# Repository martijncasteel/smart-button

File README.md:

# Smart-button
Simple shield for Nodemcu v3 with three cherrymx buttons. The different buttons can control Elgato lights or Hue Lights. This project came forward out the necesity of having a button to control a Elgato keylight without having to use their app.

## Usage
Start by setting up [source/secrets.h](code/smart-button/secrets.h.example) with your wifi credentials and bridge ip-address if you want to add Hue lights. Adjust your smart-button.ino as you wish to use, below some information on setting up the different lights. 

### Elgato Keylight
Controlling a Elgato keylight can be done with the following;
```c++
// connect with light in setup
Light * keyLight = new ElgatoLight("http://elgato-key-light-air-1857.local:9123/elgato/lights");
keyLight->toggle();
```

### Hue Lights and groups
Controlling a Hue light is a little bit more complex, the device needs to create an account on the Hue bridge. When starting the device it will connect to the wifi configured in `secret.h`. When the light is blinking you'll have to press the button on the bridge. When pressed you'll have 30 seconds to press the first button on our shield.
```c++
  // connect to bridge, create and store user in eeprom
  address_t bridge = HueLight::connect(HUE_BRIDGE, LED_BUILTIN, buttons[0]);

  // control a specific light
  Light * diningLight = new HueLight(bridge, 3);

  // controll all lights within a group
  Light * livingRoom = new HueGroup(bridge, 7);
  livingRoom->toggle();
```

## Shield

A simple shield made using Kicad to give it a nice aesthetic, you can also use a simple breadboard with simple buttons. The pins use an interal pull-up resistor. When the pin is connected to ground the button is pressed. You can find the source in [pcb](pcb/) and the assembly in [assembly](assembly/) to send to your preferred manufacturer.

## License
This project is licensed under the MIT license. See [LICENSE](LICENSE.md) for more information.

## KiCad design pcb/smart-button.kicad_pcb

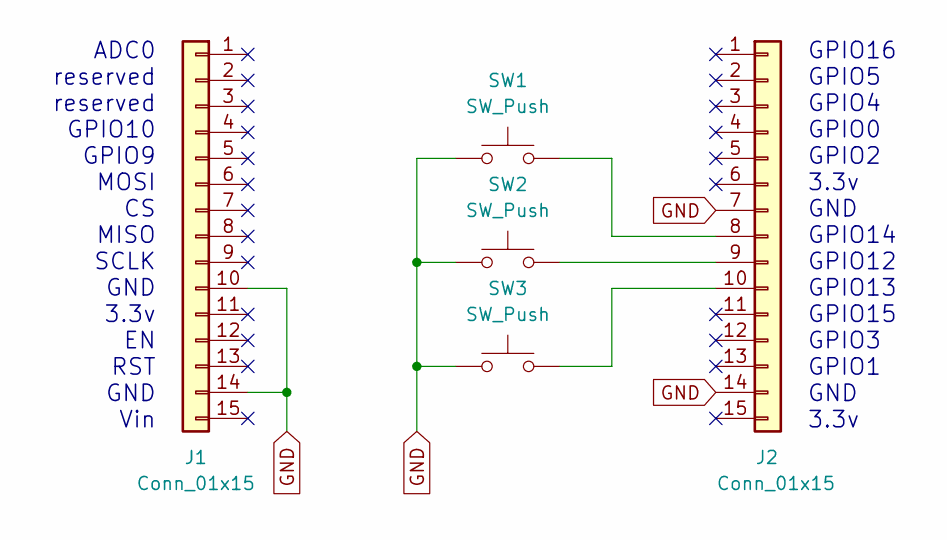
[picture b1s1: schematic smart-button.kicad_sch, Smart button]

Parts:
J1, J2: Conn_01x15; PinHeader_1x15_P2.54mm_Vertical
SW1, SW2, SW3: SW_Push; SW_Cherry_MX_1.00u_PCB

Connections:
GND: J1.10, J1.14, J2.7, J2.14, SW1.1, SW2.1, SW3.1
unnamed: J2.8, SW1.2
unnamed: J2.9, SW2.2
unnamed: J2.10, SW3.2

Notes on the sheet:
ADC0 reserved reserved GPIO10 GPIO9 MOSI CS MISO SCLK GND 3.3v EN RST GND Vin
GPIO16 GPIO5 GPIO4 GPIO0 GPIO2 3.3v GND GPIO14 GPIO12 GPIO13 GPIO15 GPIO3 GPIO1 GND 3.3v

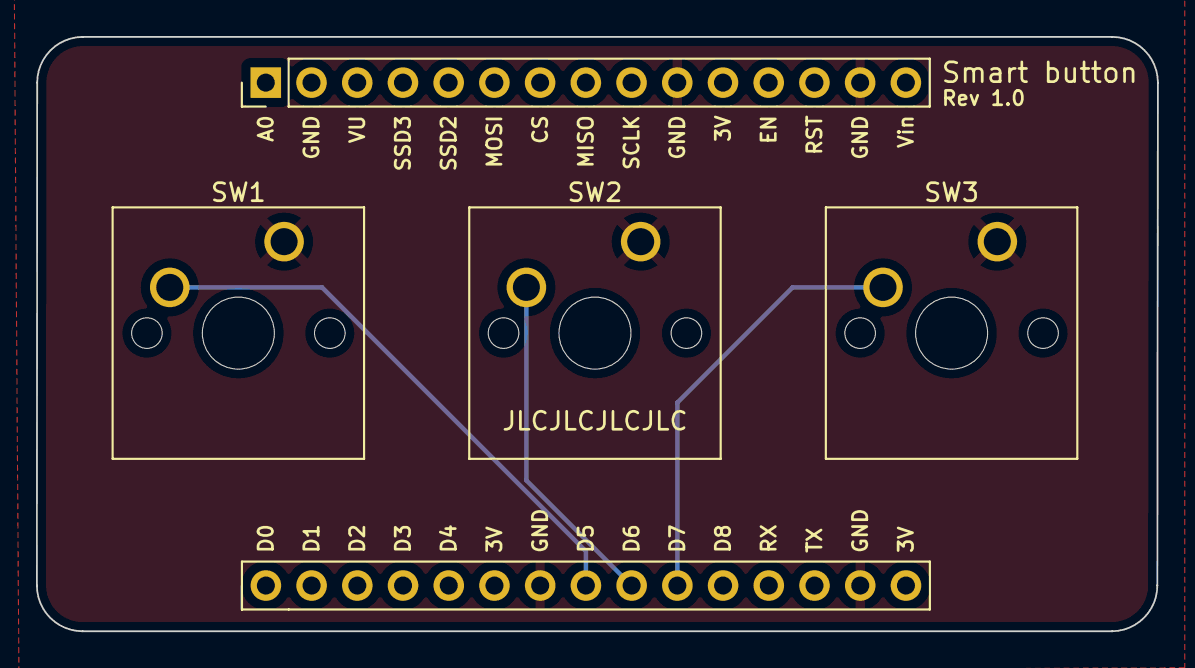
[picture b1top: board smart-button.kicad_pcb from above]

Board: 2 copper layers, 62.3 x 33.0 mm, 5 parts (0 on the bottom side), 4 nets.

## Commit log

2022-04-04 Initial version, with internal pull-up
2022-04-04 Added resistors seperatly
2022-04-05 Using simple pins not connected to leds and verified internal pull-up resistors
2022-04-07 Added code for keylight and started for hue lights
2022-04-09 Restructured folder and get hue light to work
2022-04-09 Added HueGroup as a copy of HueLight
2022-04-09 Added settings for a hue remote
2022-04-09 Settings for a remote in the study, for the keylight
2022-04-09 Started working on README
2022-04-09 Added hue lights to README
2022-04-09 Added some images
2022-04-09 Fixed path to example secrets.h
2022-04-09 Minor fix in README
2022-04-26 Final changes, it works :)
2022-04-27 Added holding a button ti change brightness
2022-04-27 Add a photo of the end result! :)
2022-04-27 Changed some names
2022-04-27 Improved hue light integration, able to cope with some values in eeprom
2022-04-27 Added example secrets file
